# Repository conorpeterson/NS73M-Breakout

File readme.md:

# NS73M-Breakout
2017 Conor Peterson (conor.p.peterson@gmail.com)

License: Creative Commons Attribution International 4.0 (CC-BY-4.0)

This is a breakout board for the Niigata Seimitsu NS73M FM transmitter chip. It
is based on a now-discontinued board formerly available from Sparkfun. Besides
the transmitter itself, there are pads for a crystal and SMT electrolytic
capacitor. Build note: the solder pad under the crystal body is intended to help
mechanically secure the package. 

Dimensions: 25mm x 17mm

Layers: 2

## Bill of Materials
```
| Ref | Spec          | Manu               | Manu Part        | Digikey #    |
| C1  | 22uF 10v      | Panasonic          | EEE-FK1A220R     | PCE3774CT-ND |
| Y1  | 32.768 kHz    | Citizen Finedevice | CFS-20632768DZBB | 300-8301-ND  |
| U1  | RF Xmitter    | Niigata Seimitsu   | NS73M            | N/A          |
| P1  | .100" x 9 pos | Sullins Connector  | PEC09SFAN        | S1212E-09-ND |
```

_Note: for runs of 5 or more, substitute P1 for 40-position breakway header
(e.g. Sullins Connector Solutions PRPC040SAAN-RC, Digikey #S1011EC-40-ND or similar)_

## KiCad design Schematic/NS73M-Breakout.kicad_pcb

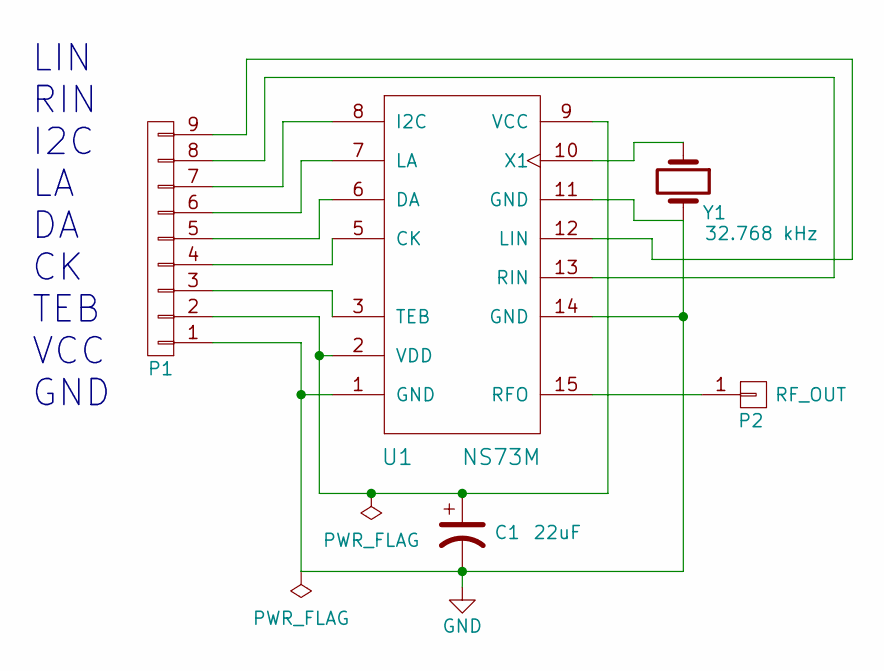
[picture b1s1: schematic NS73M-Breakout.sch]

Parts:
C1: 22uF; CP_Elec_4x4.5
P1: HEADER; Pin_Header_Angled_1x09_Pitch2.54mm_Reverse
P2: RF_OUT; Pin_Header_Angled_1x01_Pitch2.54mm
U1: NS73M; NS73M-DFN
Y1: 32.768 kHz; Crystal_C26-LF_d2.1mm_l6.5mm_Horizontal_1EP_style1

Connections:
GND: C1.2, P1.1, U1.1 (GND), U1.11 (GND), U1.14 (GND), Y1.2
unnamed: C1.1, P1.2, U1.2 (VDD), U1.9 (VCC)
unnamed: P1.3, U1.3 (TEB)
unnamed: P1.4, U1.5 (CK)
unnamed: P1.5, U1.6 (DA)
unnamed: P1.6, U1.7 (LA)
unnamed: P1.7, U1.8 (I2C)
unnamed: P1.8, U1.13 (RIN)
unnamed: P1.9, U1.12 (LIN)
unnamed: P2.1, U1.15 (RFO)
unnamed: U1.10 (X1), Y1.1

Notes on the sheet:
LIN RIN I2C LA DA CK TEB VCC GND

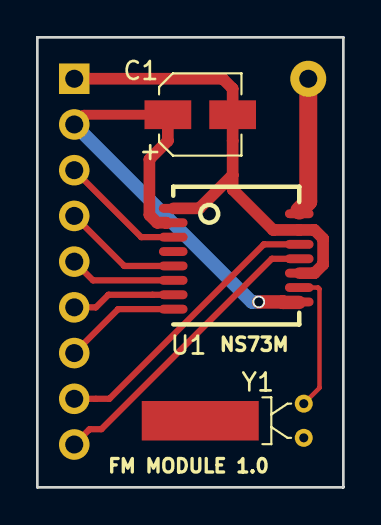
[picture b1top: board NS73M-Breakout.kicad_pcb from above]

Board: 2 copper layers, 17.0 x 25.0 mm, 5 parts (0 on the bottom side), 11 nets.

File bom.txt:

NS73M-Breakout Bill Of Materials
Prepared by Conor Peterson (conor.p.peterson@gmail.com)
May 3, 2017


| Schem. Ref | Spec          | Manu               | Manu Part        | Digikey #    |
| C1         | 22uF 10v      | Panasonic          | EEE-FK1A220R     | PCE3774CT-ND |
| Y1         | 32.768 kHz    | Citizen Finedevice | CFS-20632768DZBB | 300-8301-ND  |
| U1         | RF Xmitter    | Niigata Seimitsu   | NS73M            | N/A          |
| P1         | .100" x 9 pos | Sullins Connector  | PEC09SFAN        | S1212E-09-ND |

Note: for runs of 5 or more, substitute P1 for 40-position breakway header.
Example: Sullins Connector Solutions PRPC040SAAN-RC, Digikey #S1011EC-40-ND

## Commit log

2017-05-03 Initial commit - basic schematic with three components
2017-05-03 Power flags, schematic passes ERC
2017-05-03 Netlist
2017-05-03 First revision of PCB including gerbers
2017-05-04 Cleaned up schematic, gerber packages, added license and PCB screencaps
2017-05-04 Added readme and minor cleanups
2017-05-04 markdown fixes in readme
2017-05-16 Photos of PCB in updated readme
